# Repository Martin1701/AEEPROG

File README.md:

# AEEPROG
An EPROM/EEPROM Programmer

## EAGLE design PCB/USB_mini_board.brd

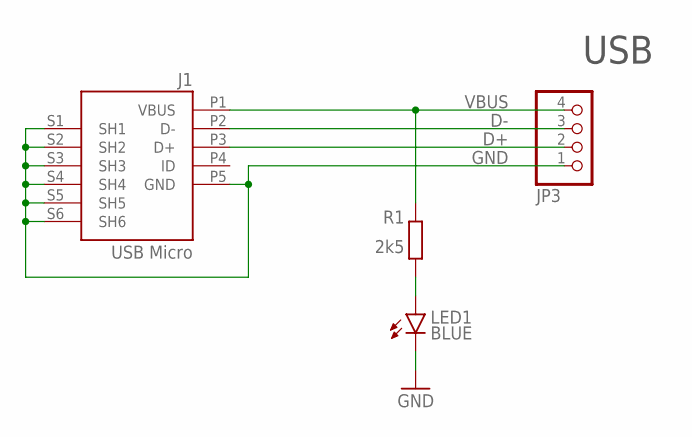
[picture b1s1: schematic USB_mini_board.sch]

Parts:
J1: USB Micro; CON2_USB_MICRO_B_AT
JP3: PINHD-1X4; 1X04
LED1: BLUE; CHIP-LED0805
R1: 2k5; R1206

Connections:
D+: J1.P3 (D+), JP3.2
D-: J1.P2 (D-), JP3.3
GND: J1.P5 (GND), J1.S1 (SH1), J1.S2 (SH2), J1.S3 (SH3), J1.S4 (SH4), J1.S5 (SH5), J1.S6 (SH6), JP3.1, LED1.C
unnamed: LED1.A, R1.2
VBUS: J1.P1 (VBUS), JP3.4, R1.1

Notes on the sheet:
USB

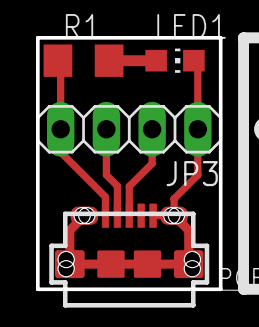
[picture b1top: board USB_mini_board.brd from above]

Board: 2 copper layers, 10.2 x 14.0 mm, 4 parts (0 on the bottom side), 5 nets.

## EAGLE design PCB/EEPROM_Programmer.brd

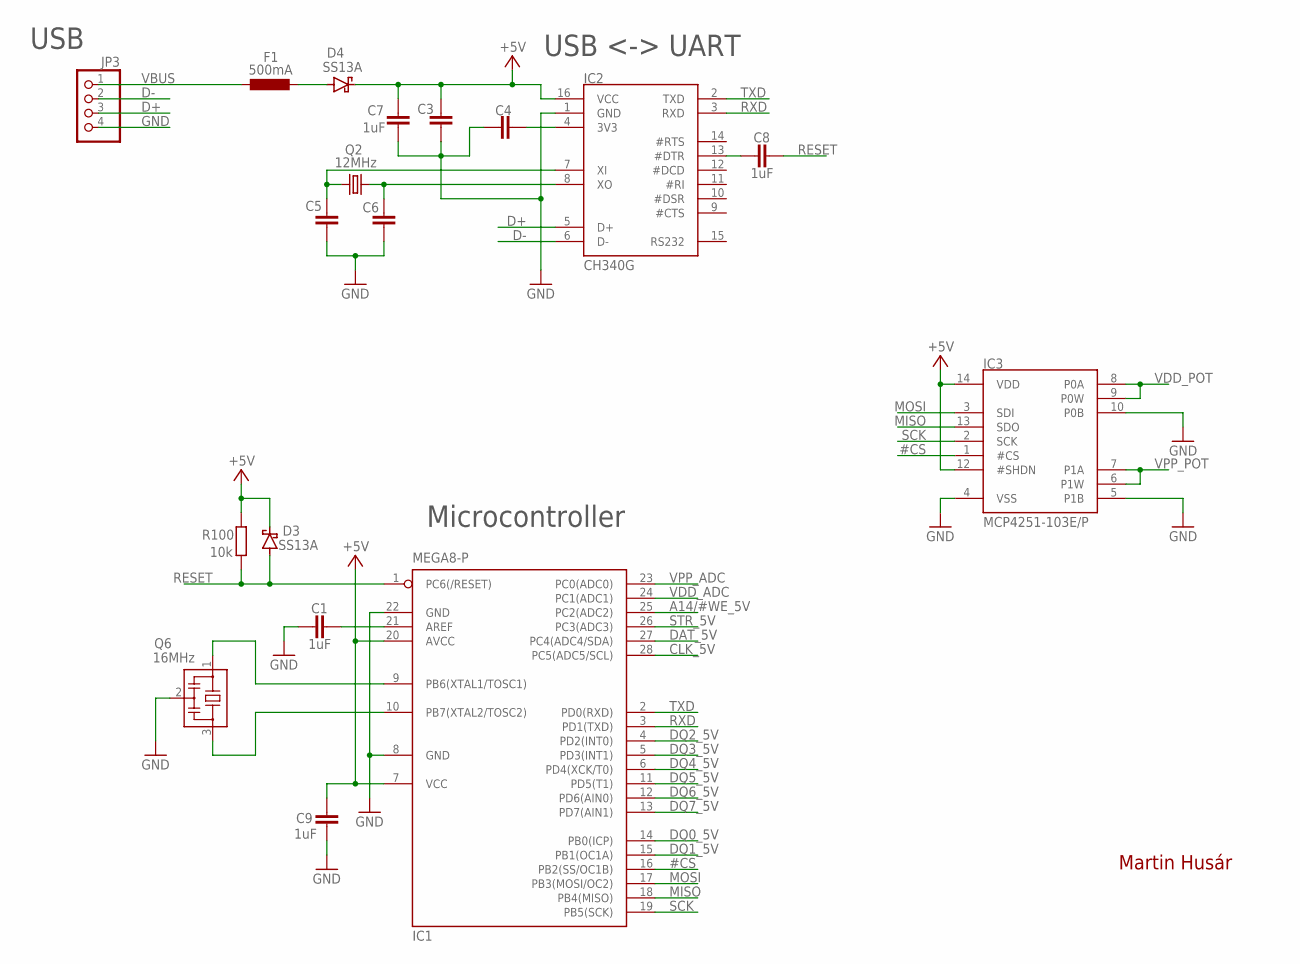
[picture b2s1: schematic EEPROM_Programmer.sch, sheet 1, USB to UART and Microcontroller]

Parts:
C1, C7, C8, C9: 1uF; C0805
C3, C4, C5, C6: C-EUC0603; C0603
D3, D4: SS13A; SOD-123_MINI-SMA
F1: 500mA; L1812
IC1: MEGA8-P; DIL28-3
IC2: CH340G; SOP16
IC3: MCP4251-103E/P; DIL14
JP3: PINHD-1X4; 1X04
Q2: 12MHz; HC49U-V
Q6: 16MHz; ZTTCS*MX
R100: 10k; R0805

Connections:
#CS: IC1.16 (PB2(SS/OC1B)), IC3.1 (#CS)
+5V: C3.2, C7.2, C9.2, D3.C, D4.C, IC1.7 (VCC), IC1.20 (AVCC), IC2.16 (VCC), IC3.12 (#SHDN), IC3.14 (VDD), R100.2; also elsewhere on the board
A14/#WE_5V: IC1.25 (PC2(ADC2)); also elsewhere on the board
CLK_5V: IC1.28 (PC5(ADC5/SCL)); also elsewhere on the board
D+: IC2.5 (D+), JP3.3
D-: IC2.6 (D-), JP3.2
DAT_5V: IC1.27 (PC4(ADC4/SDA)); also elsewhere on the board
DQ0_5V: IC1.14 (PB0(ICP)); also elsewhere on the board
DQ1_5V: IC1.15 (PB1(OC1A)); also elsewhere on the board
DQ2_5V: IC1.4 (PD2(INT0)); also elsewhere on the board
DQ3_5V: IC1.5 (PD3(INT1)); also elsewhere on the board
DQ4_5V: IC1.6 (PD4(XCK/T0)); also elsewhere on the board
DQ5_5V: IC1.11 (PD5(T1)); also elsewhere on the board
DQ6_5V: IC1.12 (PD6(AIN0)); also elsewhere on the board
DQ7_5V: IC1.13 (PD7(AIN1)); also elsewhere on the board
GND: C1.1, C3.1, C4.2, C5.2, C6.2, C7.1, C9.1, IC1.8 (GND), IC1.22 (GND), IC2.1 (GND), IC3.4 (VSS), IC3.5 (P1B), IC3.10 (P0B), JP3.4, Q6.2; also elsewhere on the board
MISO: IC1.18 (PB4(MISO)), IC3.13 (SDO)
MOSI: IC1.17 (PB3(MOSI/OC2)), IC3.3 (SDI)
unnamed: IC1.9 (PB6(XTAL1/TOSC1)), Q6.1
unnamed: IC1.10 (PB7(XTAL2/TOSC2)), Q6.3
unnamed: C1.2, IC1.21 (AREF)
unnamed: C8.1, IC2.13 (#DTR)
unnamed: C5.1, IC2.7 (XI), Q2.2
unnamed: C6.1, IC2.8 (XO), Q2.1
unnamed: C4.1, IC2.4 (3V3)
unnamed: D4.A, F1.2
RESET: C8.2, D3.A, IC1.1 (PC6(/RESET)), R100.1
RXD: IC1.3 (PD1(TXD)), IC2.3 (RXD)
SCK: IC1.19 (PB5(SCK)), IC3.2 (SCK)
STR_5V: IC1.26 (PC3(ADC3)); also elsewhere on the board
TXD: IC1.2 (PD0(RXD)), IC2.2 (TXD)
VBUS: F1.1, JP3.1
VDD_ADC: IC1.24 (PC1(ADC1)); also elsewhere on the board
VDD_POT: IC3.8 (P0A), IC3.9 (P0W); also elsewhere on the board
VPP_ADC: IC1.23 (PC0(ADC0)); also elsewhere on the board
VPP_POT: IC3.6 (P1W), IC3.7 (P1A); also elsewhere on the board

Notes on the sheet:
Martin Husár
USB
USB <-> UART
Microcontroller

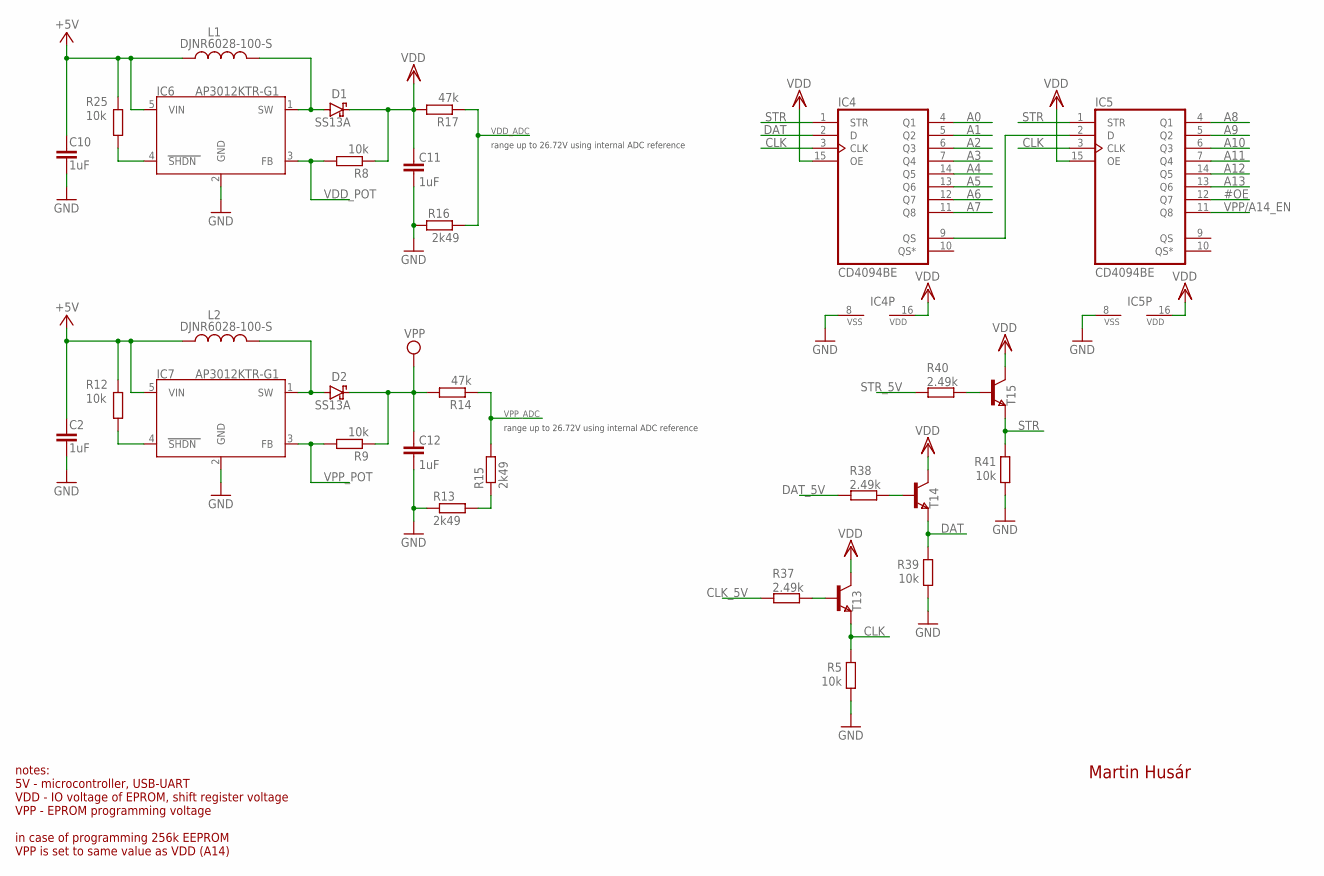
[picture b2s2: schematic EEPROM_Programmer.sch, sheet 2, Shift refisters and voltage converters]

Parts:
C2, C10, C11, C12: 1uF; C0805
D1, D2: SS13A; SOD-123_MINI-SMA
IC4, IC5: CD4094BE; DIL16
IC6, IC7: AP3012KTR-G1; SOT23-5
L1, L2: DJNR6028-100-S; INDUCTOR
R5, R8, R9, R12, R25, R39, R41: 10k; R0805
R13, R15, R16: 2k49; R0805
R14, R17: 47k; R1206
R37, R38, R40: 2.49k; R0805
T13, T14, T15: NPN; SOT-23

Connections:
#OE: IC5.12 (Q7); also elsewhere on the board
+5V: C2.1, C10.1, IC6.5 (VIN), IC7.5 (VIN), L1.P$1 (1), L2.P$1 (1), R12.2, R25.2; also elsewhere on the board
A0: IC4.4 (Q1); also elsewhere on the board
A1: IC4.5 (Q2); also elsewhere on the board
A2: IC4.6 (Q3); also elsewhere on the board
A3: IC4.7 (Q4); also elsewhere on the board
A4: IC4.14 (Q5); also elsewhere on the board
A5: IC4.13 (Q6); also elsewhere on the board
A6: IC4.12 (Q7); also elsewhere on the board
A7: IC4.11 (Q8); also elsewhere on the board
A8: IC5.4 (Q1); also elsewhere on the board
A9: IC5.5 (Q2); also elsewhere on the board
A10: IC5.6 (Q3); also elsewhere on the board
A11: IC5.7 (Q4); also elsewhere on the board
A12: IC5.14 (Q5); also elsewhere on the board
A13: IC5.13 (Q6); also elsewhere on the board
CLK: IC4.3 (CLK), IC5.3 (CLK), R5.2, T13.2 (E)
CLK_5V: R37.2; also elsewhere on the board
DAT: IC4.2 (D), R39.2, T14.2 (E)
DAT_5V: R38.2; also elsewhere on the board
GND: C2.2, C10.2, C11.2, C12.2, IC4.8 (VSS), IC5.8 (VSS), IC6.2 (GND), IC7.2 (GND), R5.1, R13.1, R16.1, R39.1, R41.1; also elsewhere on the board
unnamed: IC4.9 (QS), IC5.2 (D)
unnamed: D1.A, IC6.1 (SW), L1.P$2 (2)
unnamed: D2.A, IC7.1 (SW), L2.P$2 (2)
unnamed: R13.2, R15.1
unnamed: R38.1, T14.3 (B)
unnamed: R40.1, T15.3 (B)
unnamed: R37.1, T13.3 (B)
SHDN: IC6.4 (SHDN), R25.1
SHDN1: IC7.4 (SHDN), R12.1
STR: IC4.1 (STR), IC5.1 (STR), R41.2, T15.2 (E)
STR_5V: R40.2; also elsewhere on the board
VDD: C11.1, D1.C, IC4.15 (OE), IC4.16 (VDD), IC5.15 (OE), IC5.16 (VDD), R8.1, R17.2, T13.1 (C), T14.1 (C), T15.1 (C); also elsewhere on the board
VDD_ADC: R16.2, R17.1; also elsewhere on the board
VDD_POT: IC6.3 (FB), R8.2; also elsewhere on the board
VPP: C12.1, D2.C, R9.1, R14.2; also elsewhere on the board
VPP/A14_EN: IC5.11 (Q8); also elsewhere on the board
VPP_ADC: R14.1, R15.2; also elsewhere on the board
VPP_POT: IC7.3 (FB), R9.2; also elsewhere on the board

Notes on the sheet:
Martin Husár
range up to 26.72V using internal ADC reference
notes: 5V - microcontroller, USB-UART VDD - IO voltage of EPROM, shift register voltage VPP - EPROM programming voltage in case of programming 256k EEPROM VPP is set to same value as VDD (A14)

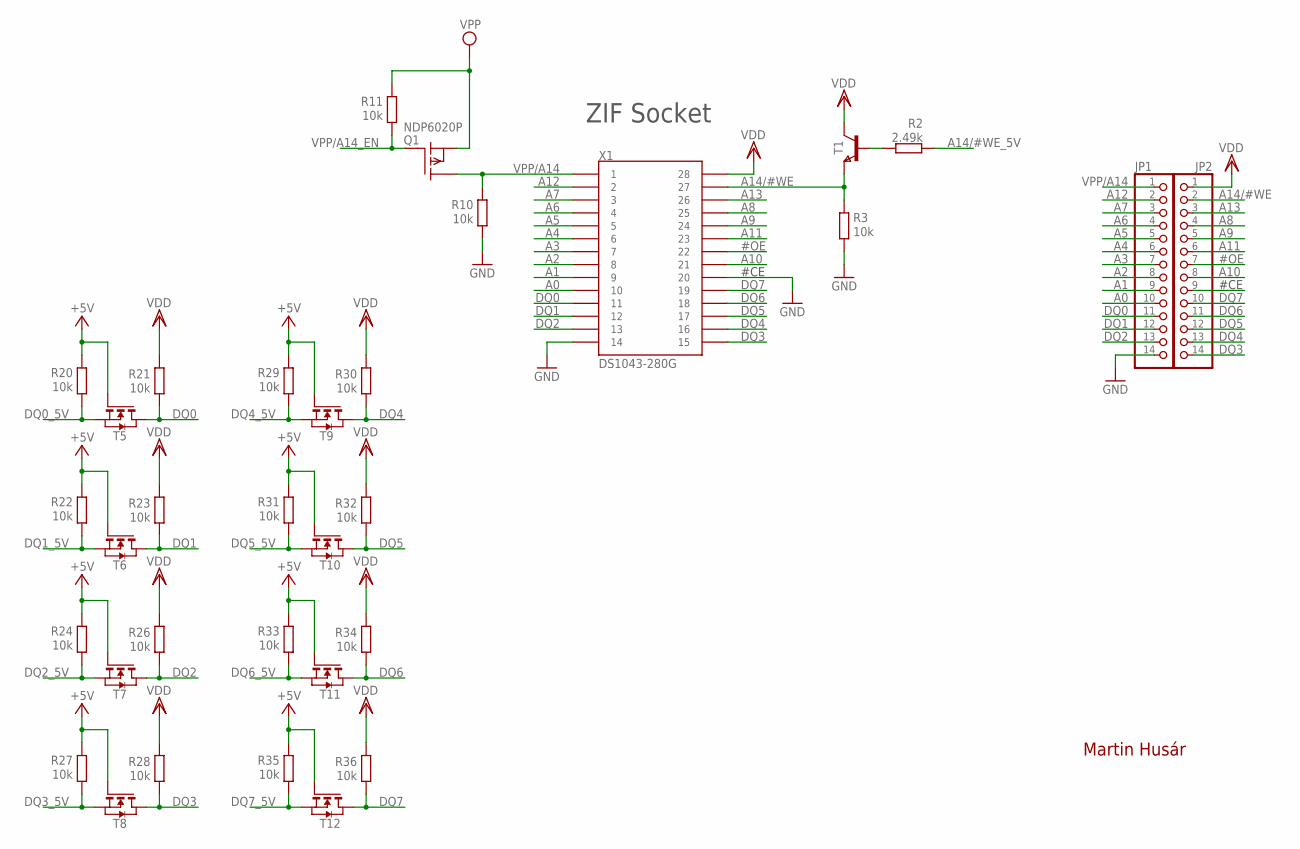
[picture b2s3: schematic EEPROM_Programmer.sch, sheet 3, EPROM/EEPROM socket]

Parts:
JP1, JP2: PINHD-1X14; 1X14
Q1: NDP6020P; TO220
R2: 2.49k; R0805
R3, R10, R11, R20, R21, R22, R23, R24, R26, R27, R28, R29, R30, R31, R32, R33, R34, R35, R36: 10k; R0805
T1: NPN; SOT-23
T5, T6, T7, T8, T9, T10, T11, T12: NMOSSOT23; SOT-23
X1: DS1043-280G

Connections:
#OE: JP2.7, X1.P22 (22); also elsewhere on the board
+5V: R20.2, R22.2, R24.2, R27.2, R29.2, R31.2, R33.2, R35.2, T5.3 (G), T6.3 (G), T7.3 (G), T8.3 (G), T9.3 (G), T10.3 (G), T11.3 (G), T12.3 (G); also elsewhere on the board
A0: JP1.10, X1.P10 (10); also elsewhere on the board
A1: JP1.9, X1.P9 (9); also elsewhere on the board
A2: JP1.8, X1.P8 (8); also elsewhere on the board
A3: JP1.7, X1.P7 (7); also elsewhere on the board
A4: JP1.6, X1.P6 (6); also elsewhere on the board
A5: JP1.5, X1.P5 (5); also elsewhere on the board
A6: JP1.4, X1.P4 (4); also elsewhere on the board
A7: JP1.3, X1.P3 (3); also elsewhere on the board
A8: JP2.4, X1.P25 (25); also elsewhere on the board
A9: JP2.5, X1.P24 (24); also elsewhere on the board
A10: JP2.8, X1.P21 (21); also elsewhere on the board
A11: JP2.6, X1.P23 (23); also elsewhere on the board
A12: JP1.2, X1.P2 (2); also elsewhere on the board
A13: JP2.3, X1.P26 (26); also elsewhere on the board
A14/#WE: JP2.2, R3.2, T1.2 (E), X1.P27 (27)
A14/#WE_5V: R2.2; also elsewhere on the board
DQ0: JP1.11, R21.1, T5.1 (D), X1.P11 (11)
DQ0_5V: R20.1, T5.2 (S); also elsewhere on the board
DQ1: JP1.12, R23.1, T6.1 (D), X1.P12 (12)
DQ1_5V: R22.1, T6.2 (S); also elsewhere on the board
DQ2: JP1.13, R26.1, T7.1 (D), X1.P13 (13)
DQ2_5V: R24.1, T7.2 (S); also elsewhere on the board
DQ3: JP2.14, R28.1, T8.1 (D), X1.P15 (15)
DQ3_5V: R27.1, T8.2 (S); also elsewhere on the board
DQ4: JP2.13, R30.1, T9.1 (D), X1.P16 (16)
DQ4_5V: R29.1, T9.2 (S); also elsewhere on the board
DQ5: JP2.12, R32.1, T10.1 (D), X1.P17 (17)
DQ5_5V: R31.1, T10.2 (S); also elsewhere on the board
DQ6: JP2.11, R34.1, T11.1 (D), X1.P18 (18)
DQ6_5V: R33.1, T11.2 (S); also elsewhere on the board
DQ7: JP2.10, R36.1, T12.1 (D), X1.P19 (19)
DQ7_5V: R35.1, T12.2 (S); also elsewhere on the board
GND: JP1.14, JP2.9, R3.1, R10.1, X1.P14 (14), X1.P20 (20); also elsewhere on the board
unnamed: R2.1, T1.3 (B)
VDD: JP2.1, R21.2, R23.2, R26.2, R28.2, R30.2, R32.2, R34.2, R36.2, T1.1 (C), X1.P28 (28); also elsewhere on the board
VPP: Q1.3 (S), R11.2; also elsewhere on the board
VPP/A14: JP1.1, Q1.2 (D), R10.2, X1.P1 (1)
VPP/A14_EN: Q1.1 (G), R11.1; also elsewhere on the board

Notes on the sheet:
Martin Husár
ZIF Socket
#CE

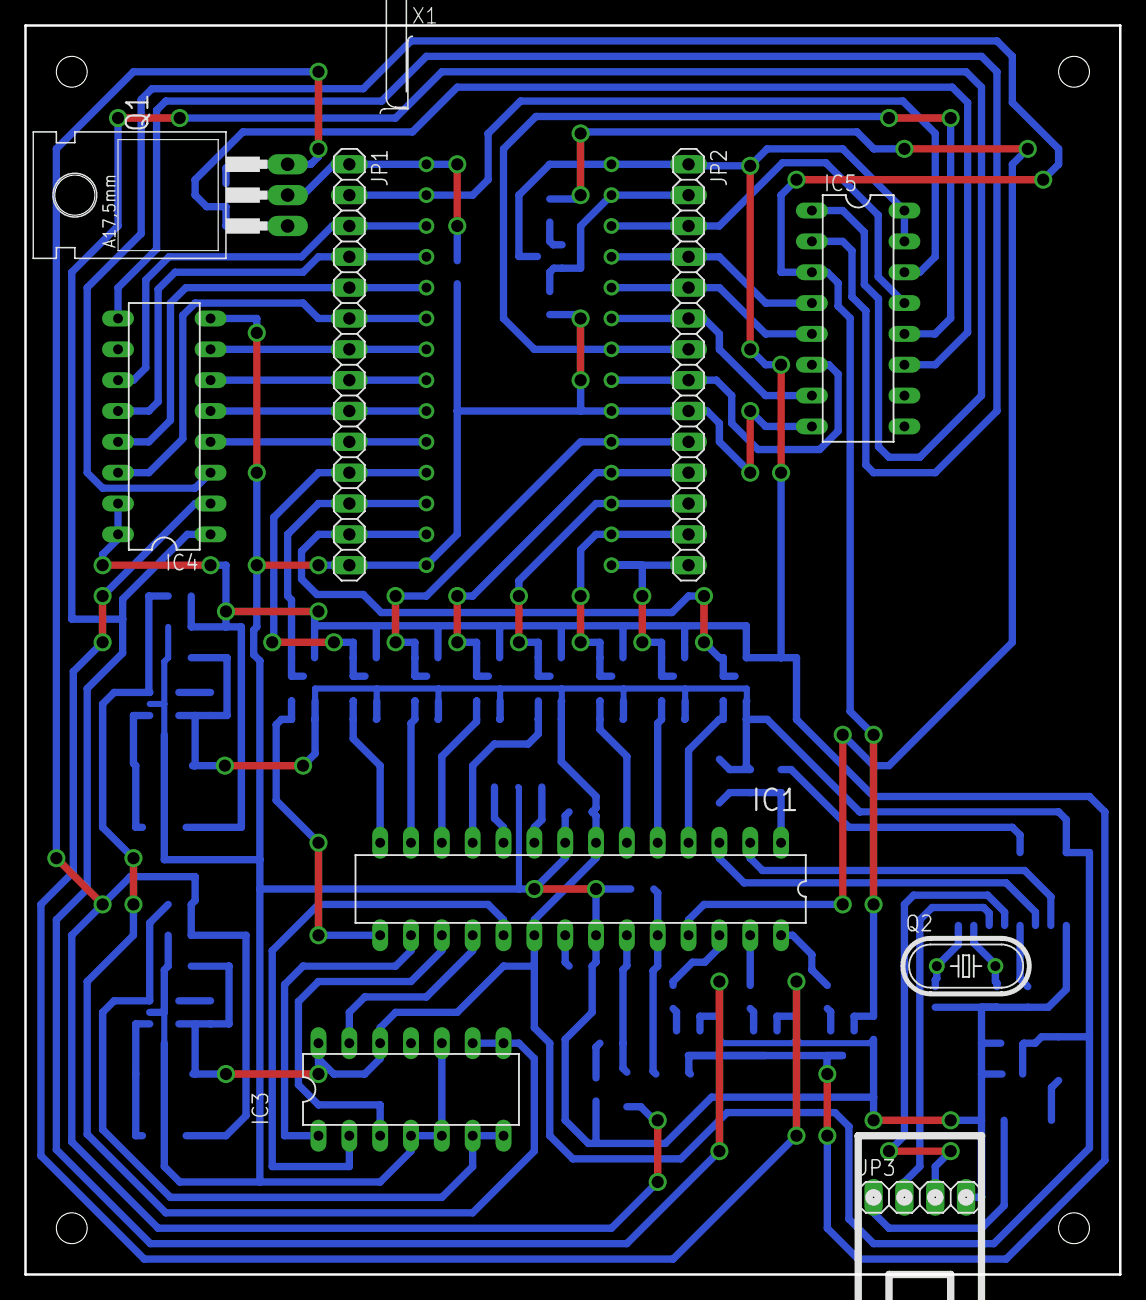
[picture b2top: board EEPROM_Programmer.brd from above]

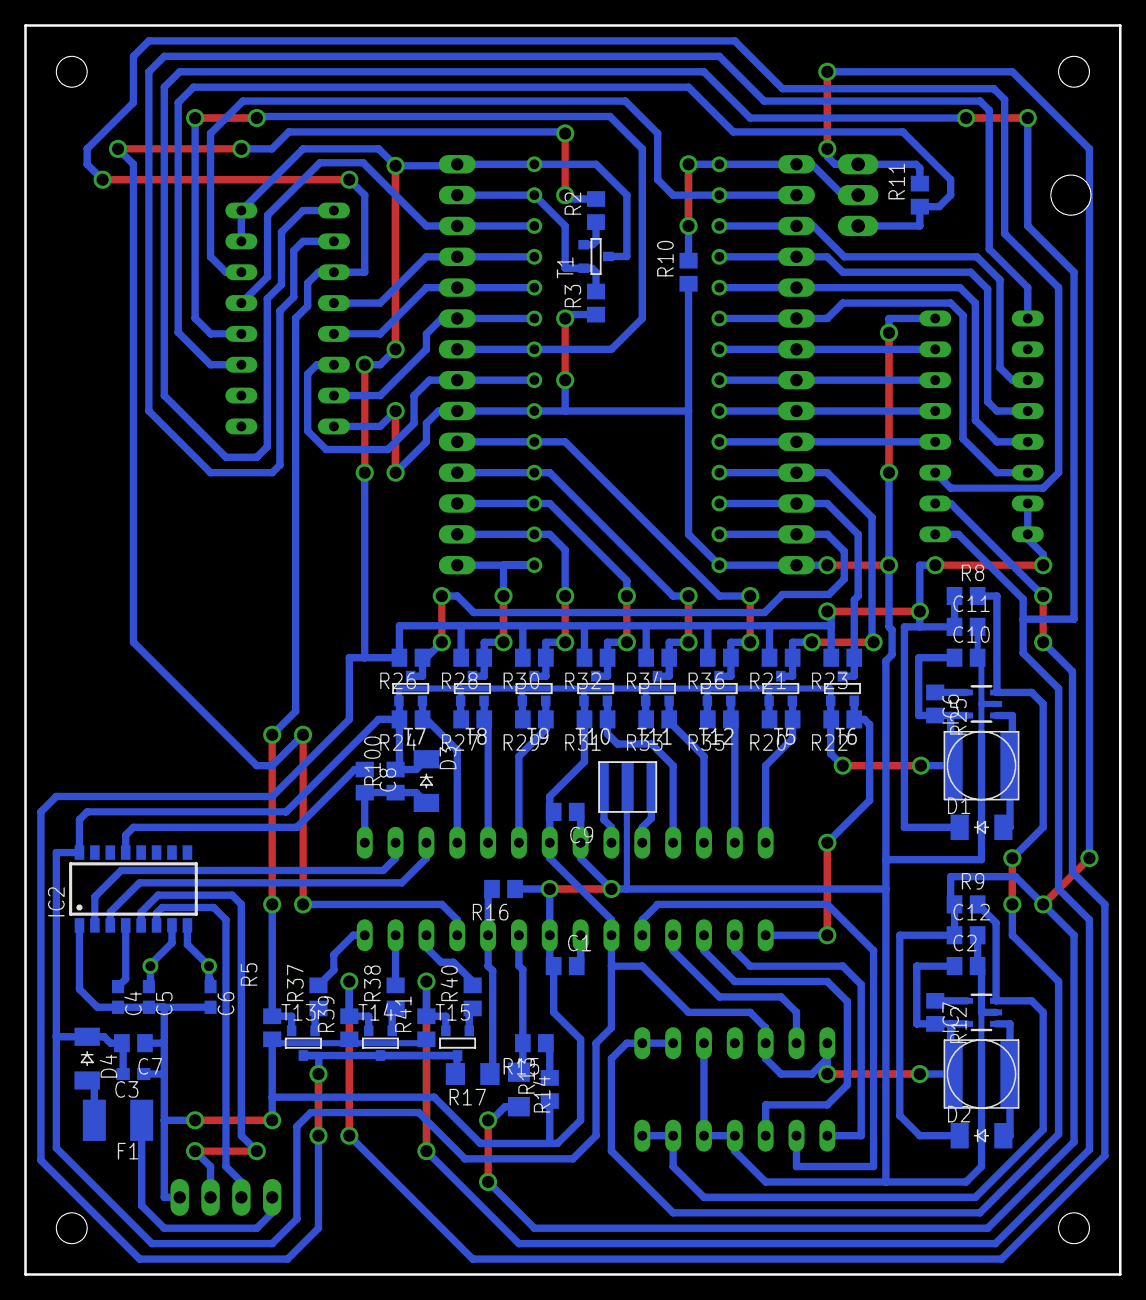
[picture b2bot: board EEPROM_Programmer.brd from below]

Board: 2 copper layers, 90.2 x 102.9 mm, 81 parts (71 on the bottom side), 77 nets.

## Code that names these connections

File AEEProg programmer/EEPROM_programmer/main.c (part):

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}
void setup_hardware(void) {
	/* port configuration */
	DDRC |= (1<<PC2) | (1<<PC3) | (1<<PC4) | (1<<PC5); // A14/#WE, STR, DAT, CLK
	DDRB |= (1<<PB5);
	//DDRB |= (1<<PB1) | (1<<PB0);
	
	PORTB &= ~(1<<PB5);

	/* ADC setup */
	ADCSRA = (1<<ADEN) | (1<<ADPS2) | (1<<ADPS1) | (1<<ADPS0);
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		PORTB = ((data & 0x03) | (PORTB & 0xFC)); // first two bits
		PORTD = ((data & 0xFC) | (PORTD & 0x03)); // all the other bits
		
		PORTC &= ~(1<<PC2); // WRITE_EN low
		_delay_us(1);
		PORTC |= (1<<PC2); // WRITE_EN high
		for(; us_delay > 0; us_delay--) {
			_delay_us(1);
		}
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void setAddress(uint16_t address, bool outputEnable, bool writeEprom) {
	if(memoryType == EPROM) {
		if(address > 0x3FFF) {
			PORTC |= (1<<PC2);
			} else {
			PORTC &= ~(1<<PC2);
		}
		shiftOut(PC4, PC5, MSBFIRST, ((address >> 8) & 0x3F) | (outputEnable ? 0x00 : 0x40) | (writeEprom ? 0x00 : 0x80));
		shiftOut(PC4, PC5, MSBFIRST, address);
		} else {
		//shiftOut(PC4, PC5, MSBFIRST, ((address >> 8) & 0x3F) | (outputEnable ? 0x00 : 0x40));
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		shiftOut(PC4, PC5, MSBFIRST, address);
	}
	PORTC &= ~(1<<PC3);
	PORTC |= (1<<PC3);
	PORTC &= ~(1<<PC3);
	_delay_us(1);
}

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
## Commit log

2024-07-10 add console app
2024-07-10 add PCB files
2024-07-10 add programmer

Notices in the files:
parts and their libraries:
Arduino-connectors: Copyright (c) 2016-2017 Arduino LLC.  All right reserved.
